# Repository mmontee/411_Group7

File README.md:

# 411_Group7<br>
This is to be use as a collaboration site for ECE411<br>

This is the Readme file. It should be mantained as an introduction and map to all the work within the Repo.<br>

Decision matrix sheet:<br>
https://docs.google.com/spreadsheets/d/1eD4bU1PSHvnIHJjQp7CIA1_oRjcmT8zQqf65oZdo7yo/edit?gid=0#gid=0<br>
Decision matrix deliverable document:<br>
https://docs.google.com/document/d/1ifG8m_yKul6lawxM7RGC06Qm2UjNfSLFXjXEhdREGek/edit?usp=sharing<br>
Gantt chart:<br>
https://pdx102634.monday.com/boards/7799755810

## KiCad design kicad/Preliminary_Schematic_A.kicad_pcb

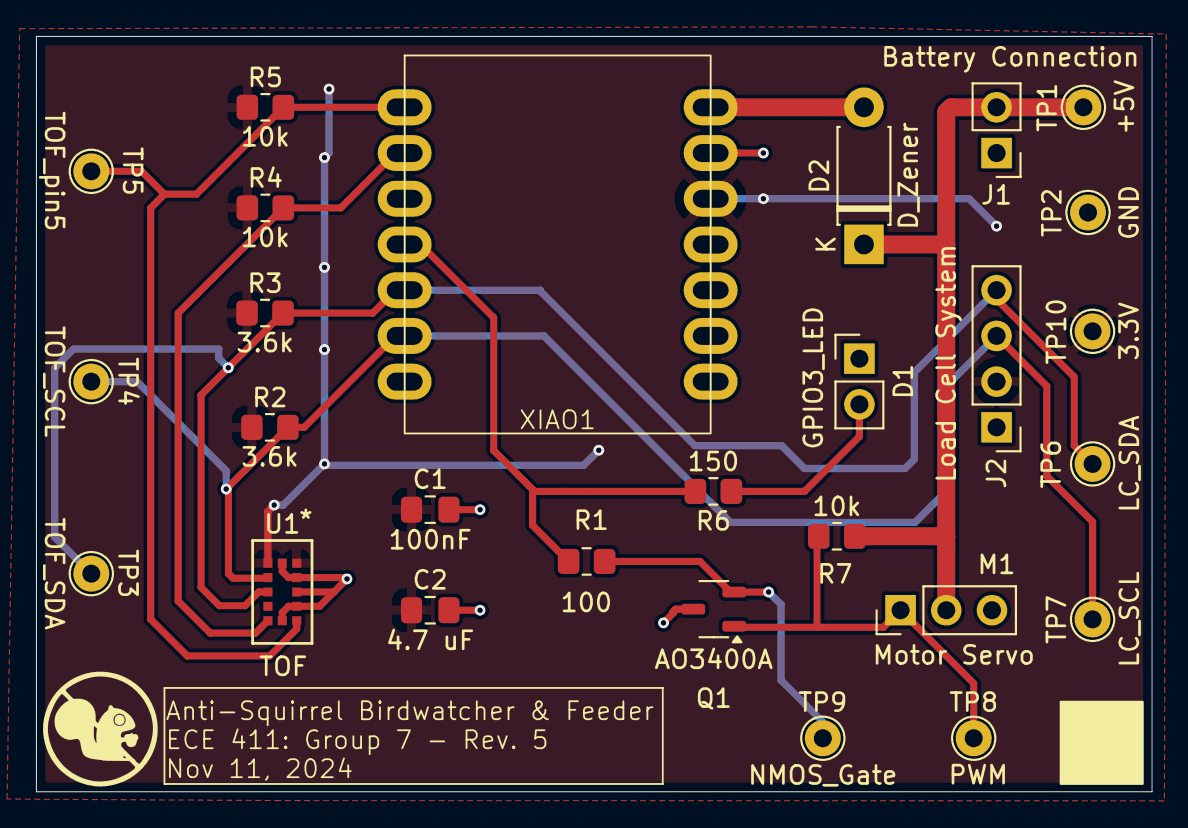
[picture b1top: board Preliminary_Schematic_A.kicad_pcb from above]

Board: 2 copper layers, 62.0 x 42.0 mm, 27 parts (0 on the bottom side), 12 nets.

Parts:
C1: 100nF; C_0805_2012Metric_Pad1.18x1.45mm_HandSolder
C2: 4.7 uF; C_0805_2012Metric_Pad1.18x1.45mm_HandSolder
D1: GPIO3_LED; PinHeader_1x02_P2.54mm_Vertical
D2: D_Zener; D_DO-41_SOD81_P7.62mm_Horizontal
J1: Battery Connection; PinHeader_1x02_P2.54mm_Vertical
J2: Load Cell System; PinHeader_1x04_P2.54mm_Vertical
M1: Motor Servo; PinHeader_1x03_P2.54mm_Vertical
Q1: AO3400A; SOT-23-3
R1: 100; R_0805_2012Metric_Pad1.20x1.40mm_HandSolder
R2, R3: 3.6k; R_0805_2012Metric_Pad1.20x1.40mm_HandSolder
R4, R5, R7: 10k; R_0805_2012Metric_Pad1.20x1.40mm_HandSolder
R6: 150; R_0805_2012Metric_Pad1.20x1.40mm_HandSolder
TP1: +5V; TestPoint_THTPad_D2.0mm_Drill1.0mm
TP2: GND; TestPoint_THTPad_D2.0mm_Drill1.0mm
TP3: TOF_SDA; TestPoint_THTPad_D2.0mm_Drill1.0mm
TP4: TOF_SCL; TestPoint_THTPad_D2.0mm_Drill1.0mm
TP5: TOF_pin5; TestPoint_THTPad_D2.0mm_Drill1.0mm
TP6: LC_SDA; TestPoint_THTPad_D2.0mm_Drill1.0mm
TP7: LC_SCL; TestPoint_THTPad_D2.0mm_Drill1.0mm
TP8: PWM; TestPoint_THTPad_D2.0mm_Drill1.0mm
TP9: NMOS_Gate; TestPoint_THTPad_D2.0mm_Drill1.0mm
TP10: 3.3V; TestPoint_THTPad_D2.0mm_Drill1.0mm
U1: TOF; time of flight
XIAO1: XIAO_QTpy

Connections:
+5V: D2.1 (K), J1.2, M1.2 (+), R7.1, TP1.1
/3.3V ESP32: C1.1, C2.1, J2.2, R2.1, R3.1, R4.1, R5.1, TP10.1, U1.1 (AVDDVCSEL), U1.11 (AVDD), XIAO1.3V3
GND: C1.2, C2.2, D1.1 (K), J1.1, J2.1, M1.3 (-), Q1.3 (S), TP2.1, U1.2 (AVSSVCSEL), U1.3 (GND), U1.4 (GN2), U1.6 (GND3), U1.12 (GND4), XIAO1.GND
unnamed: D1.2 (A), R6.1
unnamed: D2.2 (A), XIAO1.5V
unnamed: J2.3, R2.2, TP4.1, TP7.1, U1.10 (SCL), XIAO1.5
unnamed: J2.4, R3.2, TP3.1, TP6.1, U1.9 (SDA), XIAO1.4
unnamed: M1.1 (PWM), Q1.1 (D), R7.2, TP8.1
unnamed: Q1.2 (G), R1.1, TP9.1
unnamed: R1.2, R6.2, XIAO1.3
unnamed: R4.2, U1.7 (GPIO1), XIAO1.1
unnamed: R5.2, TP5.1, U1.5 (XSHUT), XIAO1.0

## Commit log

2024-10-16 Project Proposal Folder and README.
2024-10-16 Added My Project Idea Proposal .pdf
2024-10-16 Update README.md
    Fixed spelling
2024-10-16 Rename Practicum Project Idea.pdf to BasicFunctionGenerator.pdf
2024-10-17 Added Birdfeeder proposal
2024-10-17 Added (Pet) Treat Dispenser idea
2024-10-29 Add files via upload
    Preliminary Schematic Rev A - KiCAD files
2024-10-29 Rename Preliminary_Schematic.kicad_prl to Preliminary_Schematic_A.kicad_prl
2024-10-29 Rename Preliminary_Schematic.kicad_sch to Preliminary_Schematic_A.kicad_sch
2024-10-29 Rename Preliminary_Schematic.kicad_pro to Preliminary_Schematic_A.kicad_pro
2024-10-29 KiCAD folder
2024-10-29 decision matrix link added to readme
2024-10-31 Add files via upload
    Preliminary Schematic Rev A PDF
2024-10-31 Added Wk - 05 Decision deliverable
2024-11-07 Create DFRobot Solar Power Manager 5V
2024-11-07 Create Product Link
2024-11-07 Create Product Wiki
2024-11-07 Documentation
2024-11-07 Create Documentation
2024-11-07 Update Documentation
2024-11-07 Create doc
2024-11-07 Bird Feeder PDS.pdf
2024-11-07 Create datasheet
2024-11-07 added camera datasheet
2024-11-13 Create Block Diagram Raw Files
2024-11-13 Add files via upload
    Raw block diagram draw.io file.
2024-11-13 Delete Functional Decomposition/Block Diagram Raw Files
    This file not necessary.
2024-11-14 Add files via upload
    PDF of functional decomposition
2024-11-14 Create URL
    URL to our bill of materials
2024-11-14 Add files via upload
    Bill of Materials Rev-A
2024-11-21 Added Design Review doc
    Wk 8 deliverable
2024-12-05 Create PDS_link
2024-12-05 Add files via upload
    URL: https://docs.google.com/document/d/1hXvPMdkKu4-qqYL7MNctZ2WegnTcsYsw-oepoJhyqHQ/edit?tab=t.0
2024-12-05 Rename Group 7 - Test Plan.pdf to Test Plan.pdf
2024-12-12 Add files via upload
    Updated/corrected revision
2024-12-13 Create photos folder
2024-12-13 Create intro
2024-12-13 added some pictures
2024-12-13 fixed folder
2024-12-13 fixed folder name
2024-12-13 Create URL
